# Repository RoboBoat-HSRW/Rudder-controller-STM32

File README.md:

# Rudder Controller – STM32

## Overview
This project is a **closed-loop control system** designed to control rudders using an STM32 microcontroller. It uses a **PID controller** for precise and stable operation and communicates via the **NMEA2000** protocol, making it suitable for marine industry applications.

---

## Features
- **Object-Oriented Design**: Uses a `Motor` class, allowing easy configuration of multiple motors with minimal code in the main file.
- **STM32 Integration**: Leverages STM32 register access for high performance, scalability, and clean code structure.
- **NMEA2000 Protocol**: Supports industry-standard marine communication.
- **Compact PCB**: Custom PCB drastically reduces size, with both power and communication delivered through a single cable.

---

## How It Works

### 1. Input Signal
- A 10-bit setpoint is received via **NMEA2000 CAN bus**.
- `512` represents the **neutral rudder position**.
- Extreme positions can be configured in software to set the desired rudder angles.

---

### 2. Feedback Loop
- Rudder position is measured by a **10k potentiometer** read via **10-bit ADC with DMA**.
- The potentiometer value is mapped to the same 0–1023 range as the input signal.
- The error is calculated as the difference between desired and actual positions.

---

### 3. Motor Control

The `Motor` class is responsible for handling rudder control:

```cpp
class Motor {
public:
    Motor(GPIO_TypeDef* port, uint16_t pin,
          volatile uint32_t* ccr,
          uint16_t* potValue, uint16_t potMax, uint16_t potMin,
          uint16_t* setPoint,
          double Kp, double Ki, double Kd);

    void controlLoop();   // Runs PID and updates CCR
    void setDirection();  // Sets motor direction based on PID output

private:
    GPIO_TypeDef* _myPort;
    uint16_t _myPin;

    uint16_t* _mypotValue;
    uint16_t _mypotMax;
    uint16_t _mypotMin;

    double _myoutput;                      // Output to CCR
    uint16_t* _mysetPoint_CAN_Rx;          // Setpoint from CAN bus

    volatile uint32_t* _ccr;               // Pointer to CCRx register

    PID pid;                               // PID controller instance
};
```
# Rudder Controller – STM32

## Overview
This project is a **closed-loop control system** designed to control rudders using an STM32 microcontroller. It uses a **PID controller** for precise and stable operation and communicates via the **NMEA2000** protocol, making it suitable for marine industry applications.

---

## Features
- **Object-Oriented Design**: Uses a `Motor` class, allowing easy configuration of multiple motors with minimal code in the main file.
- **STM32 Integration**: Leverages STM32 register access for high performance, scalability, and clean code structure.
- **NMEA2000 Protocol**: Supports industry-standard marine communication.
- **Compact PCB**: Custom PCB drastically reduces size, with both power and communication delivered through a single cable.

---

## How It Works

### 1. Input Signal
- A 10-bit setpoint is received via **NMEA2000 CAN bus**.
- `512` represents the **neutral rudder position**.
- Extreme positions can be configured in software to set the desired rudder angles.

---

### 2. Feedback Loop
- Rudder position is measured by a **10k potentiometer** read via **10-bit ADC with DMA**.
- The potentiometer value is mapped to the same 0–1023 range as the input signal.
- The error is calculated as the difference between desired and actual positions.

---

### 3. Motor Control

The `Motor` class is responsible for handling rudder control:

```cpp
class Motor {
public:
    Motor(GPIO_TypeDef* port, uint16_t pin,
          volatile uint32_t* ccr,
          uint16_t* potValue, uint16_t potMax, uint16_t potMin,
          uint16_t* setPoint,
          double Kp, double Ki, double Kd);

    void controlLoop();   // Runs PID and updates CCR
    void setDirection();  // Sets motor direction based on PID output

private:
    GPIO_TypeDef* _myPort;
    uint16_t _myPin;

    uint16_t* _mypotValue;
    uint16_t _mypotMax;
    uint16_t _mypotMin;

    double _myoutput;                      // Output to CCR
    uint16_t* _mysetPoint_CAN_Rx;          // Setpoint from CAN bus

    volatile uint32_t* _ccr;               // Pointer to CCRx register

    PID pid;                               // PID controller instance
};
```
- PID values can be changed during runtime via bash over CAN (NMEA2000), without updating the firmware.

---

### 5. Working Principle

```cpp
void Motor::setDirection() {
    HAL_GPIO_WritePin(_myPort, _myPin, (_myoutput > 0) ? GPIO_PIN_SET : GPIO_PIN_RESET);
}

void Motor::controlLoop() {
    setDirection();
    pid.compute();
    if ((_myoutput > 0 && *_mypotValue < _mypotMax) ||
        (_myoutput < 0 && *_mypotValue > _mypotMin)) {
        *_ccr = static_cast<uint32_t>((_myoutput < 0) ? -_myoutput : _myoutput);
    } else {
        *_ccr = 0;
    }
}
```
- **`setDirection()`**: Controls the motor's rotation direction.
- **`controlLoop()`**: Updates the PWM duty cycle based on PID output and ensures the shaft stays within defined bounds.

---

### Components

- **Microcontroller**: STM32F302RB – Reads input signals, processes feedback, and controls PWM output.
- **Custom PCB**: Contains STM32 MCU, switching regulator, connectors, and CAN transceiver.
- **Motor Driver**: MDDS10 – Dual-channel motor driver for controlling direction and speed.
- **Encoder**: 10k potentiometer – Measures rudder shaft position for feedback.

---

### PCB Design

The custom PCB was developed with several key advantages:

- **Size Reduction**: Final module is over 50% smaller, helping to reduce enclosure costs.
- **Tighter Integration**: Power regulation and CAN transceiver are integrated directly onto the board.
- **Cost Efficiency**: Approximate cost is **€25 per board**.
  - Cheaper than Arduino R4 (€31).
  - Slightly more than STM32 Nucleo, but includes **native NMEA2000 support** which Nucleo lacks.

**Conclusion**: The custom PCB offers a more functional and cost-effective solution for real-world production systems.

<p align="center"><b>STM32 Custom Board - Front and Back</b></p>

<p align="center"><b>Comparison: Custom PCB vs Arduino-based System</b></p>

---

### Example Initialization

```cpp
Motor motor_left(GPIOA, GPIO_PIN_4,     // Direction pin
                 &(TIM2->CCR1),         // PWM output (CCR register)
                 &adc_value[0],         // ADC DMA input
                 740, 240,              // Potentiometer max/min
                 &CanMessage[0],        // Setpoint from CAN
                 5.0, 0.0, 0.0);        // PID values

while (1) {
    // motor_left.controlLoop();
    // motor_right.controlLoop();
}

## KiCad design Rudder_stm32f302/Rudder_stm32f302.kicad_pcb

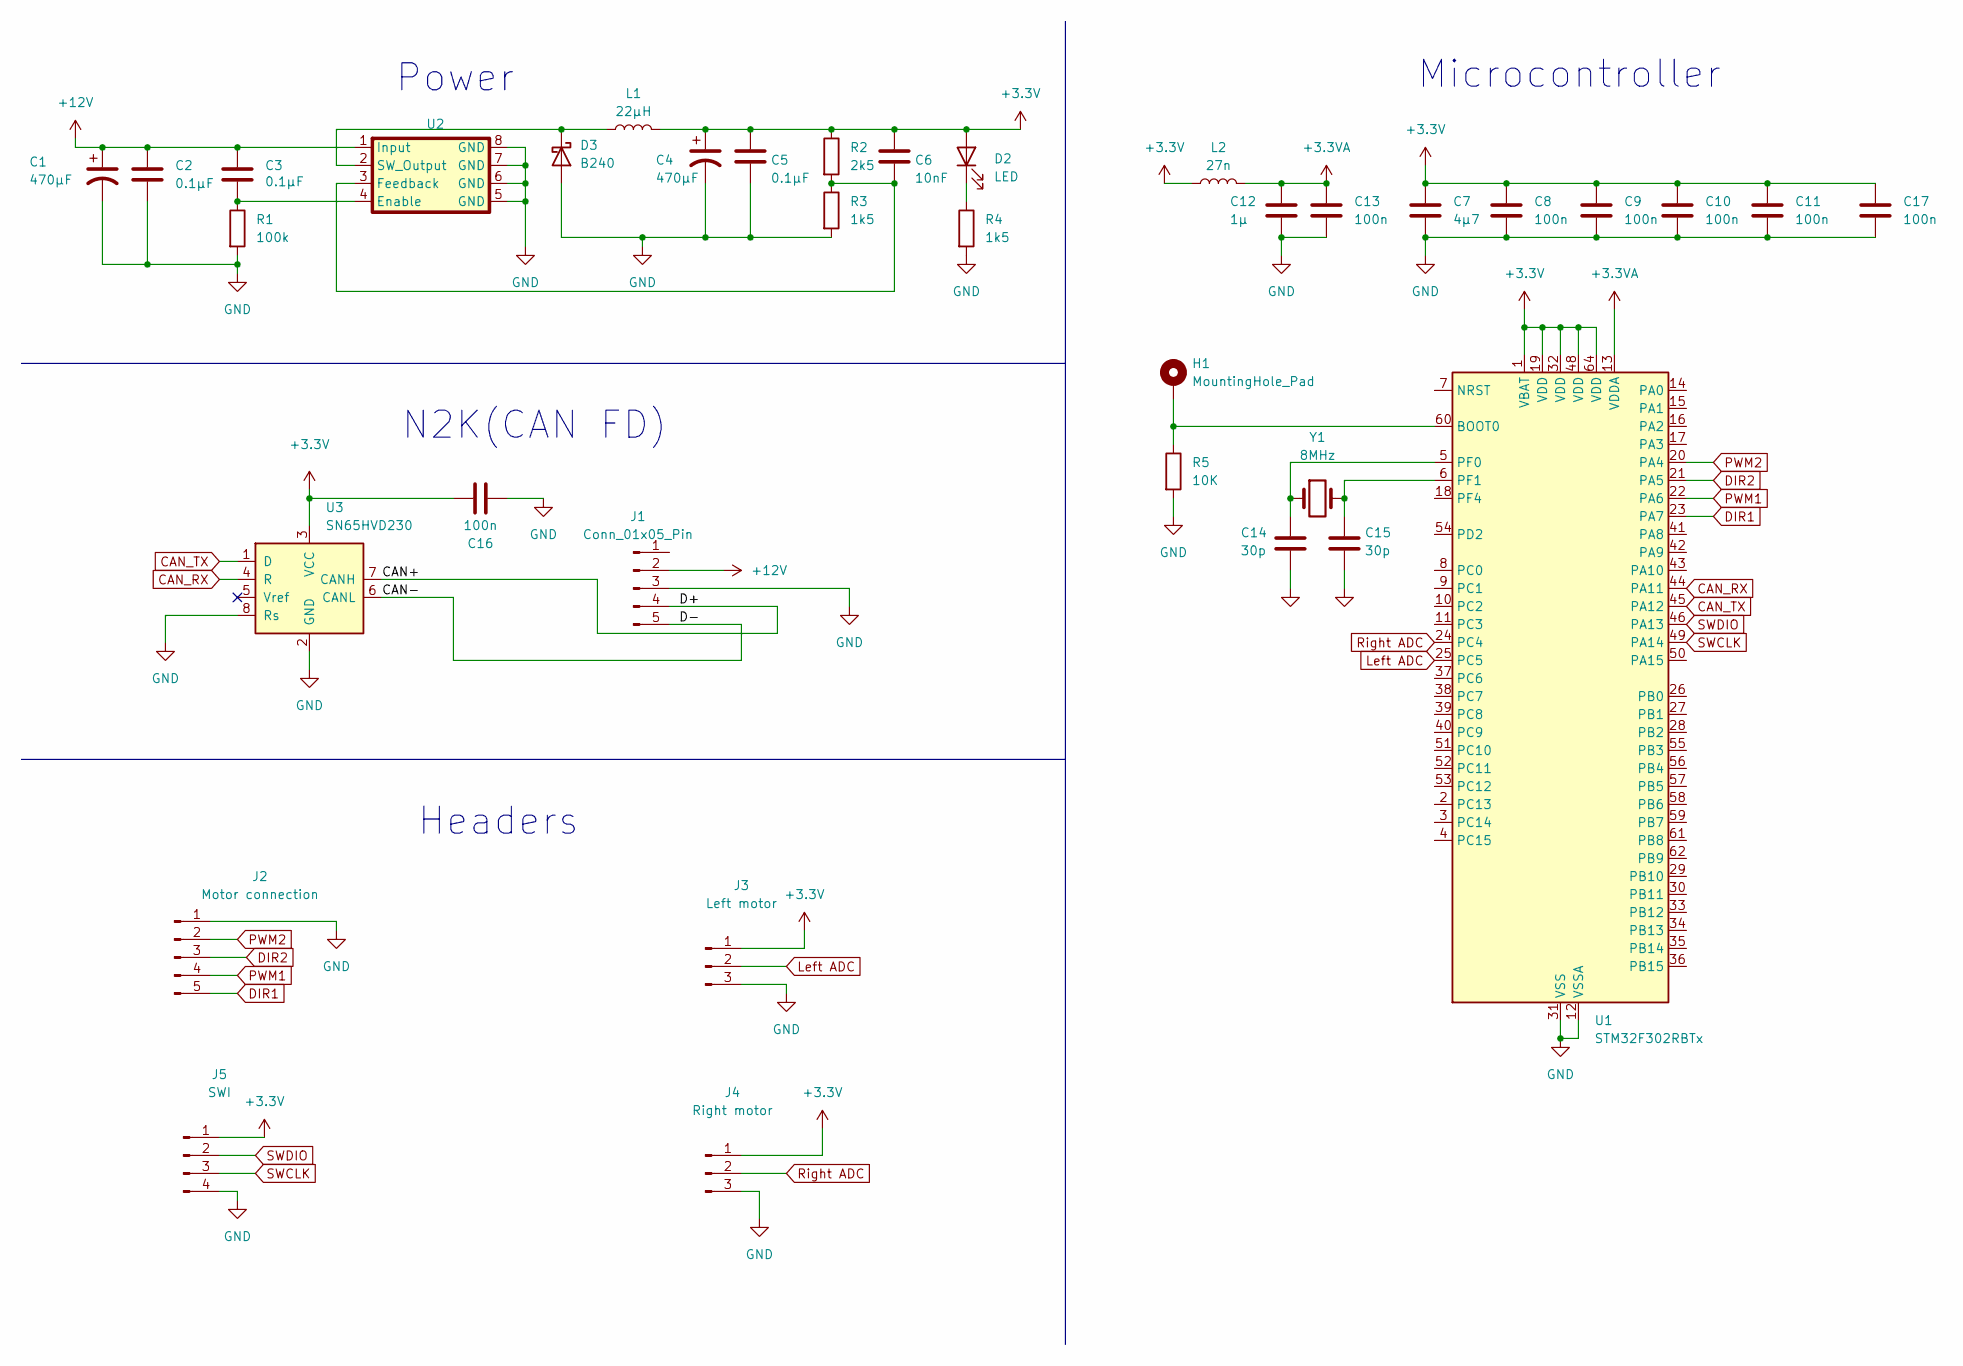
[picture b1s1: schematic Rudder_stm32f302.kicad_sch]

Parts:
C1, C4: 470µF; C_Elec_10x10.2
C2, C3, C5: 0.1µF; C_1206_3216Metric
C6: 10nF; C_1206_3216Metric
C7: 4µ7; CP_EIA-6032-20_AVX-F_Pad2.25x2.35mm_HandSolder
C8, C9, C10, C11, C13, C16, C17: 100n; C_1206_3216Metric
C12: 1µ; C_1206_3216Metric
C14, C15: 30p; C_1206_3216Metric
D2: LED; LED_1206_3216Metric
D3: B240; D_SMB
H1: MountingHole_Pad; PinHeader_1x01_P2.54mm_Vertical
J1: Conn_01x05_Pin; m12_5pol
J2: Motor connection; PinHeader_1x05_P2.54mm_Vertical
J3: Left motor; PinHeader_1x03_P2.54mm_Vertical
J4: Right motor; PinHeader_1x03_P2.54mm_Vertical
J5: SWI; JST_EH_S4B-EH_1x04_P2.50mm_Horizontal
L1: 22µH; L_Taiyo-Yuden_NR-80xx
L2: 27n; L_1206_3216Metric
R1: 100k; R_1206_3216Metric
R2: 2k5; R_1206_3216Metric
R3, R4: 1k5; R_1206_3216Metric
R5: 10K; R_1206_3216Metric
U1: STM32F302RBTx; LQFP-64_10x10mm_P0.5mm
U2: SOIC-8_3.9x4.9mm_P1.27mm
U3: SN65HVD230; SOIC-8_3.9x4.9mm_P1.27mm
Y1: 8MHz; Crystal_SMD_HC49-SD

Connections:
+3.3V: C4.1, C5.1, C6.1, C7.1, C8.1, C9.1, C10.1, C11.1, C16.1, C17.1, D2.2 (A), J3.1, J4.1, J5.1, L1.2, L2.1, R2.1, U1.1 (VBAT), U1.19 (VDD), U1.32 (VDD), U1.48 (VDD), U1.64 (VDD), U3.3 (VCC)
+3.3VA: C12.1, C13.1, L2.2, U1.13 (VDDA)
+12V: C1.1, C2.1, C3.1, J1.2, U2.1 (Input)
/CAN+: J1.4, U3.7 (CANH)
/CAN-: J1.5, U3.6 (CANL)
CAN_RX: U1.44 (PA11), U3.4 (R)
CAN_TX: U1.45 (PA12), U3.1 (D)
DIR1: J2.5, U1.23 (PA7)
DIR2: J2.3, U1.21 (PA5)
GND: C1.2, C2.2, C4.2, C5.2, C7.2, C8.2, C9.2, C10.2, C11.2, C12.2, C13.2, C14.2, C15.2, C16.2, C17.2, D3.2 (A), J1.3, J2.1, J3.3, J4.3, J5.4, R1.2, R3.2, R4.2, R5.2, U1.12 (VSSA), U1.31 (VSS), U1.47 (VSS), U1.63 (VSS), U2.5 (GND), U2.6 (GND), U2.7 (GND), U2.8 (GND), U3.2 (GND), U3.8 (Rs)
Left ADC: J3.2, U1.25 (PC5)
unnamed: D2.1 (K), R4.1
unnamed: D3.1 (K), L1.1, U2.2 (SW_Output)
unnamed: H1.1, R5.1, U1.60 (BOOT0)
unnamed: C14.1, U1.5 (PF0), Y1.1
unnamed: C15.1, U1.6 (PF1), Y1.2
unnamed: C3.2, R1.1, U2.4 (Enable)
unnamed: C6.2, R2.2, R3.1, U2.3 (Feedback)
PWM1: J2.4, U1.22 (PA6)
PWM2: J2.2, U1.20 (PA4)
Right ADC: J4.2, U1.24 (PC4)
SWCLK: J5.3, U1.49 (PA14)
SWDIO: J5.2, U1.46 (PA13)

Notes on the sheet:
Power
Microcontroller
N2K(CAN FD)
Headers

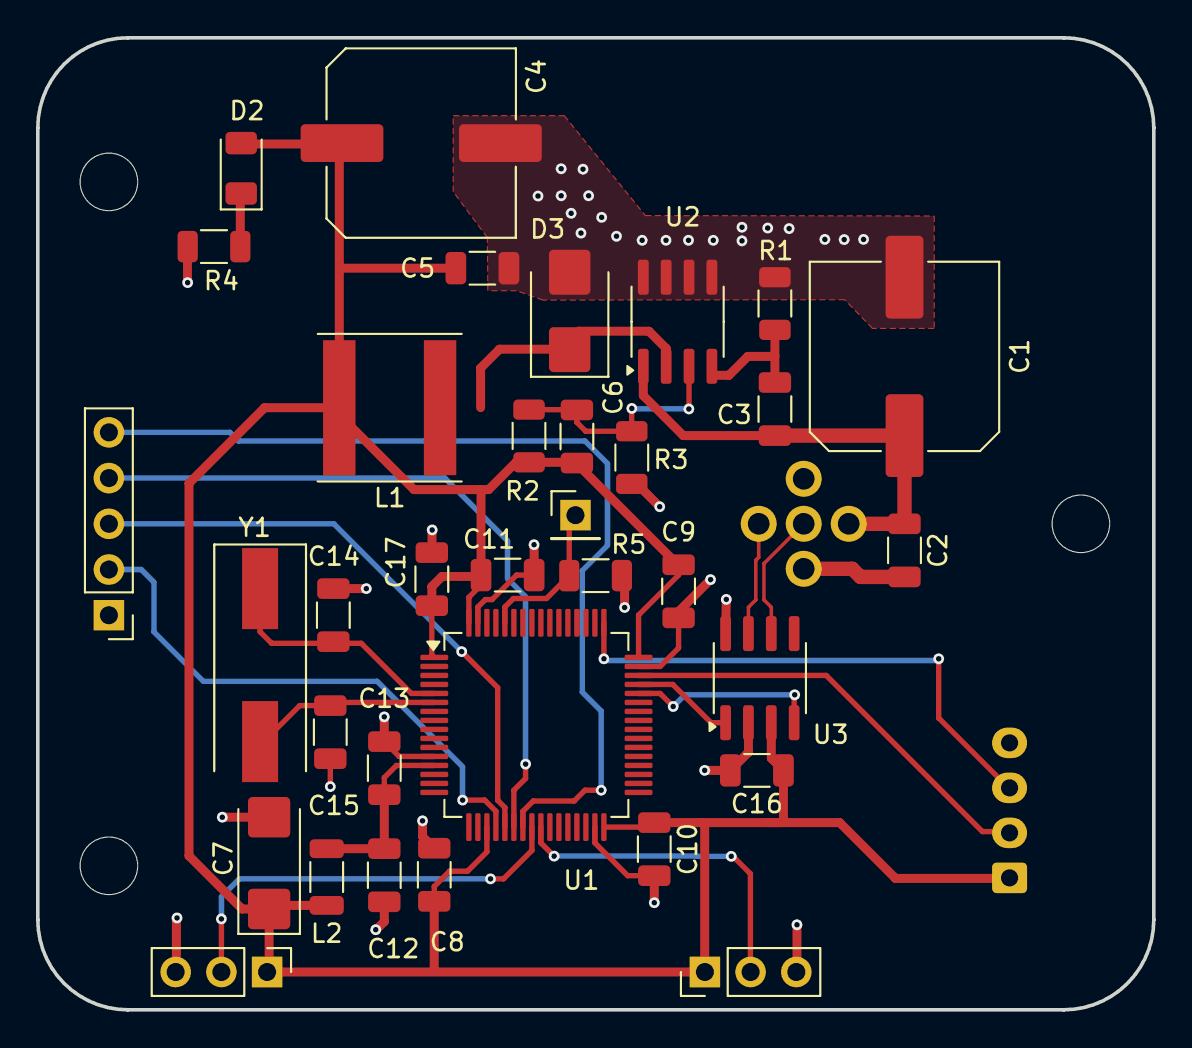
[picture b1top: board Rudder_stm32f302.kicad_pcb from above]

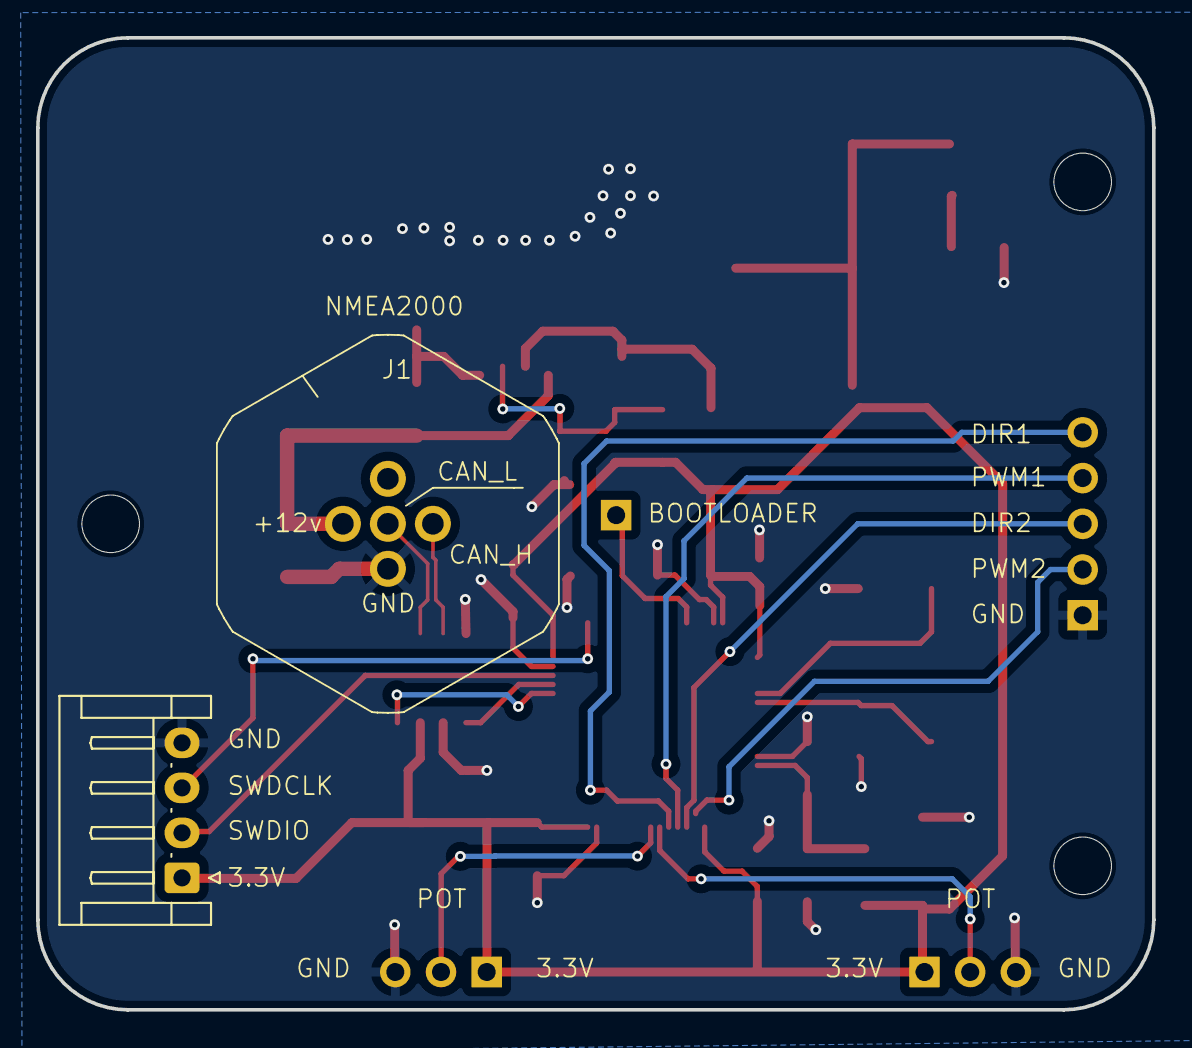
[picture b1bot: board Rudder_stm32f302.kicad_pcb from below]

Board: 2 copper layers, 62.0 x 54.0 mm, 36 parts (2 on the bottom side), 23 nets.

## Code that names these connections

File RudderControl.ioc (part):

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Mcu.Name=STM32F302R(B-C)Tx
Mcu.Package=LQFP64
Mcu.UserName=STM32F302RBTx
PA11.Mode=CAN_Activate
PA11.Signal=CAN_RX
PA12.Mode=CAN_Activate
PA12.Signal=CAN_TX
PA13.Mode=Serial_Wire
PA13.Signal=SYS_JTMS-SWDIO
PA14.Mode=Serial_Wire
PA14.Signal=SYS_JTCK-SWCLK
PA4.GPIOParameters=GPIO_Label
PA4.GPIO_Label=DIR1
PA4.Signal=GPIO_Output
PA5.GPIOParameters=GPIO_Label
PA5.GPIO_Label=PWM1
PA5.Signal=S_TIM2_CH1_ETR
PA6.GPIOParameters=GPIO_Label
PA6.GPIO_Label=DIR2
PA6.Signal=GPIO_Output
PA7.GPIOParameters=GPIO_Label
PA7.GPIO_Label=PWM2
PA7.Mode=PWM Generation1 CH1N
PA7.Signal=TIM1_CH1N
PC4.Mode=IN5-Single-Ended
PC4.Signal=ADC2_IN5
PC5.Mode=IN11-Single-Ended
PC5.Signal=ADC2_IN11
PF0-OSC_IN.GPIOParameters=GPIO_Label
PF0-OSC_IN.GPIO_Label=XTAL1
PF0-OSC_IN.Mode=HSE-External-Oscillator
PF0-OSC_IN.Signal=RCC_OSC_IN
PF1-OSC_OUT.GPIOParameters=GPIO_Label
PF1-OSC_OUT.GPIO_Label=XTAL2
PF1-OSC_OUT.Mode=HSE-External-Oscillator
PF1-OSC_OUT.Signal=RCC_OSC_OUT
RCC.HSEPLLFreq_Value=8000000
RCC.HSE_VALUE=8000000
RCC.SYSCLKFreq_VALUE=72000000
RCC.SYSCLKSourceVirtual=RCC_SYSCLKSOURCE_PLLCLK
board=custom

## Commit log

2025-06-30 Create temp
